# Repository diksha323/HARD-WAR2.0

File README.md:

# Smart Pillars

Road Safety is a big concern for police and such smart pillars will help to reduce accidents. This will be a useful installation where camera and other sensors will instantly alert drivers regarding the movement of vehicles so that they can take saftey precautions.

This project aims at number plate detection of vehicles on road using the ANPR technique and measure their speed in real-time.
The centralised data of over speeding vehicles is generated and  person is notified through whatsapp once the Automatic Challan is cut off. Additionally, the honking system installed alerts the drivers about approaching vehicles from the other blind fold end or U-turns.

## Tools and Tech Stacks
- Opencv
- Numpy
- Pandas
- Matplotlib
- Pandas
- PyTesseract
- PyWhatkit
- Arduino

## Optimizations
- Yolo v5 model for efficient object detection
- Tesseract OCR for accuracy in ANPR upto 95%
- Raspberry Pi as processing unit

## Screenshots

ANPR<br />

https://github.com/monalisa22/Smart_Pillars/assets/100671634/5ca5fe03-d03a-4011-aa27-ba0d5a04cee6

Number Plate <br />

Automatic Challan<br />

User interface on Remote App<br />

Prototype Setup<br />

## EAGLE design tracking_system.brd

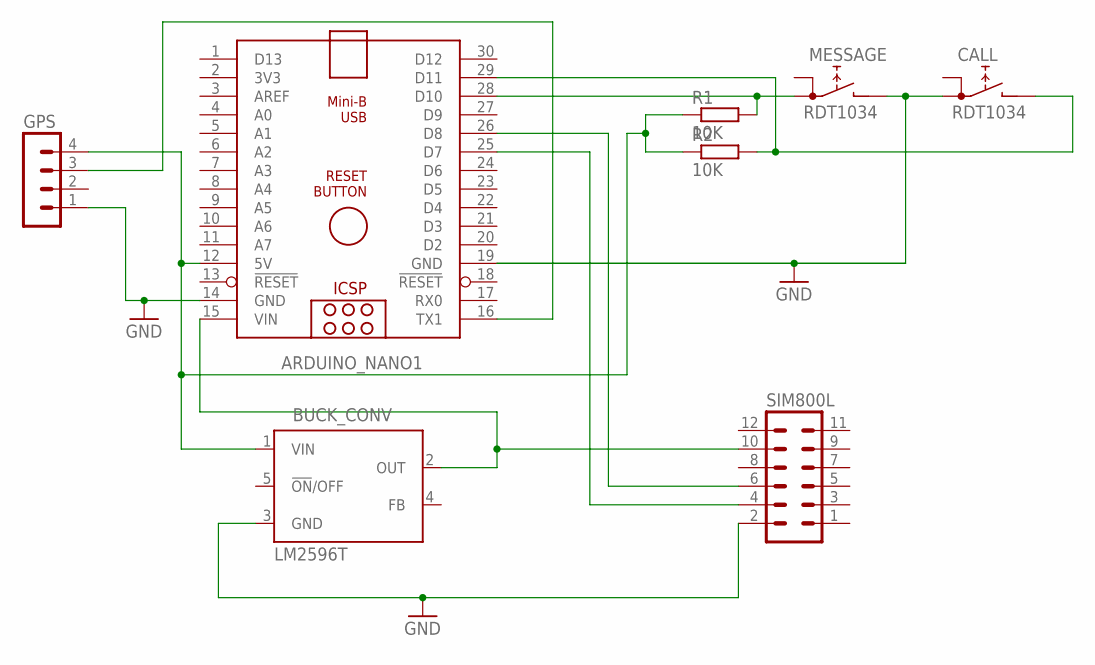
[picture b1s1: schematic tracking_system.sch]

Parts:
ARDUINO_NANO1: ARDUINO_NANO
BUCK_CONV: LM2596T; T05D
CALL: RDT1034
GPS: MA04-1
MESSAGE: RDT1034
R1, R2: 10K; 0207/10
SIM800L: MA06-2

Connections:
GND: ARDUINO_NANO1.14 (GND), ARDUINO_NANO1.19 (GND), BUCK_CONV.3 (GND), CALL.A1, GPS.1, MESSAGE.B, SIM800L.2
unnamed: ARDUINO_NANO1.16 (TX1), GPS.3
unnamed: ARDUINO_NANO1.12 (5V), BUCK_CONV.1 (VIN), GPS.4, R1.1, R2.1
unnamed: ARDUINO_NANO1.28 (D10), MESSAGE.A1, R1.2
unnamed: ARDUINO_NANO1.25 (D7), SIM800L.4
unnamed: ARDUINO_NANO1.29 (D11), CALL.B, R2.2
unnamed: ARDUINO_NANO1.26 (D8), SIM800L.6
unnamed: ARDUINO_NANO1.15 (VIN), BUCK_CONV.2 (OUT), SIM800L.10

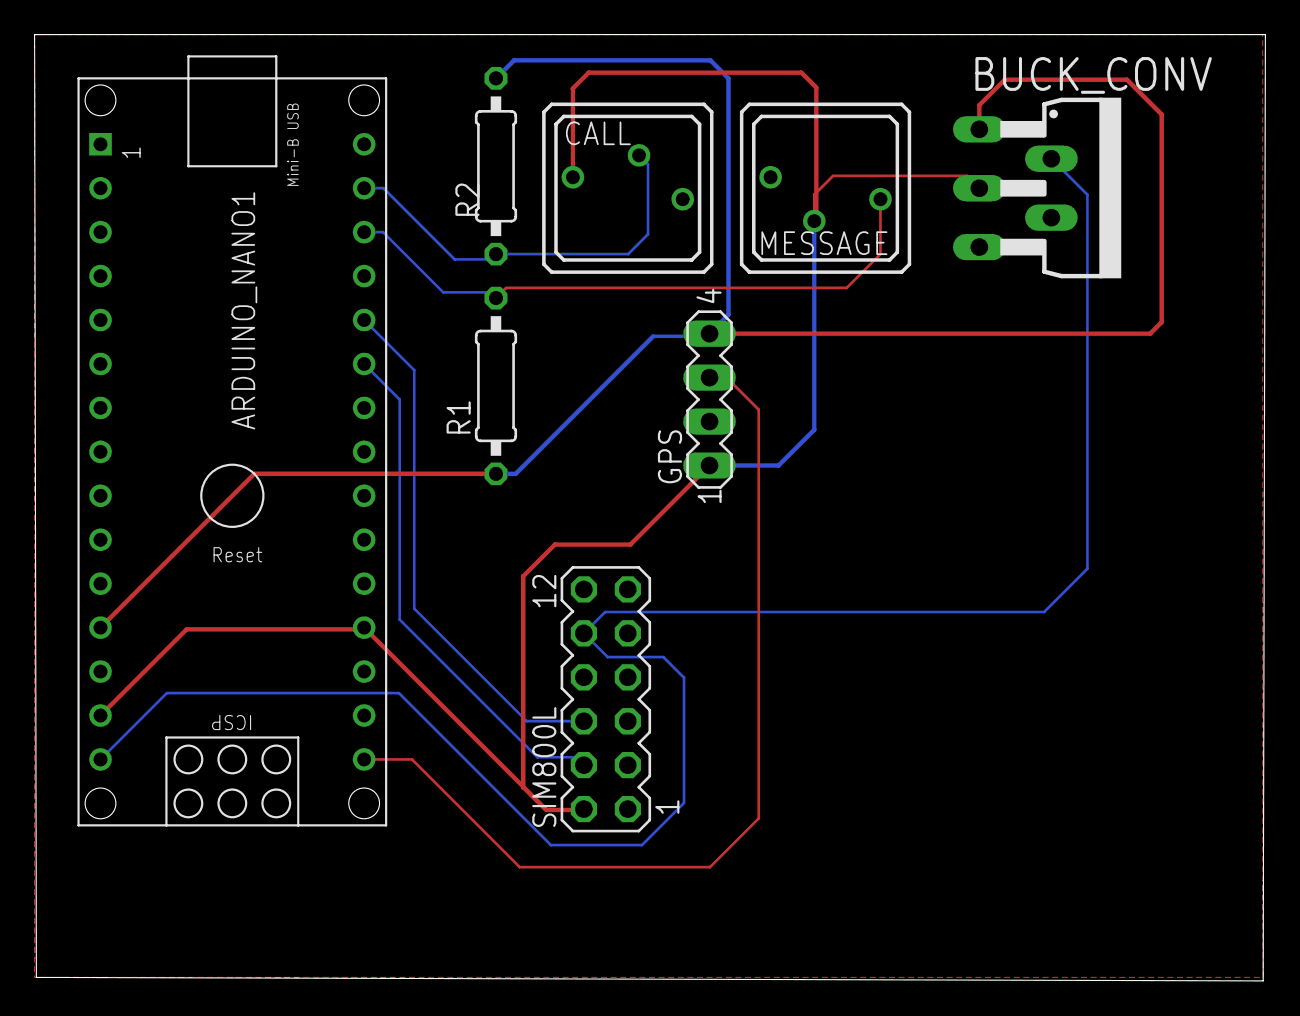
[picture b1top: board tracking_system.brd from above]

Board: 2 copper layers, 71.1 x 54.7 mm, 8 parts (0 on the bottom side), 8 nets.
